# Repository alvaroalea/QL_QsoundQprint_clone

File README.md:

# SINCLAIR QL QsoundQprint Sound and Paralel Printer port interface

(C) 2022 Alvaro Alea Fernandez

License under: CERN Open Hardware Licence Version 2 - Strongly Reciprocal

https://ohwr.org/cern_ohl_s_v2.txt

I try to follow the original desing as much as possible, with some licenses:

- It's 10mm short, to fit in a 10x10cm, that is a lot cheaps if order PCB.
- The 7805 regulator board and the output Jack was modify.
- I use a electrolitic capacitor instead the original tantalo one.
- There are some jumper to allow a future ACB stereo mix.

This project can not be possible without the help of silvester, that tracked a fault in the schematic and Marcel Kilgus that develop a new ROM with a qsound device and a pt3 player.

I test with ROM versions 1.10, 1.31 and 1.40 and work as expected, new ROM do not have the printer routines, but have a new options used by the pt3 player. 

You can use a 2764 eprom or a W27C512 flash, that is much more cheap and easy to use.

This board user the default Motorola 68K inteface as described in the documentation of AY-3-8910 PSG. with a 6821 PIA as a glue between the QL and the PSG, in the info folder you can found aditional information about this chips or the interface.

The card have full 8bit I/O in the PSG without use, and another 8 bits in the PIA, also the pins of the paralel port are directly wired to the PSG, and are bidirectional, so can be used for other propouses.

The board use the E signal as a clock for the PSG, this cause that the PSG work in a very low frecuency, below the minimun indicated in the datasheet, and also this cause that tunes from Spectrum or other systems, can not be directly converted.

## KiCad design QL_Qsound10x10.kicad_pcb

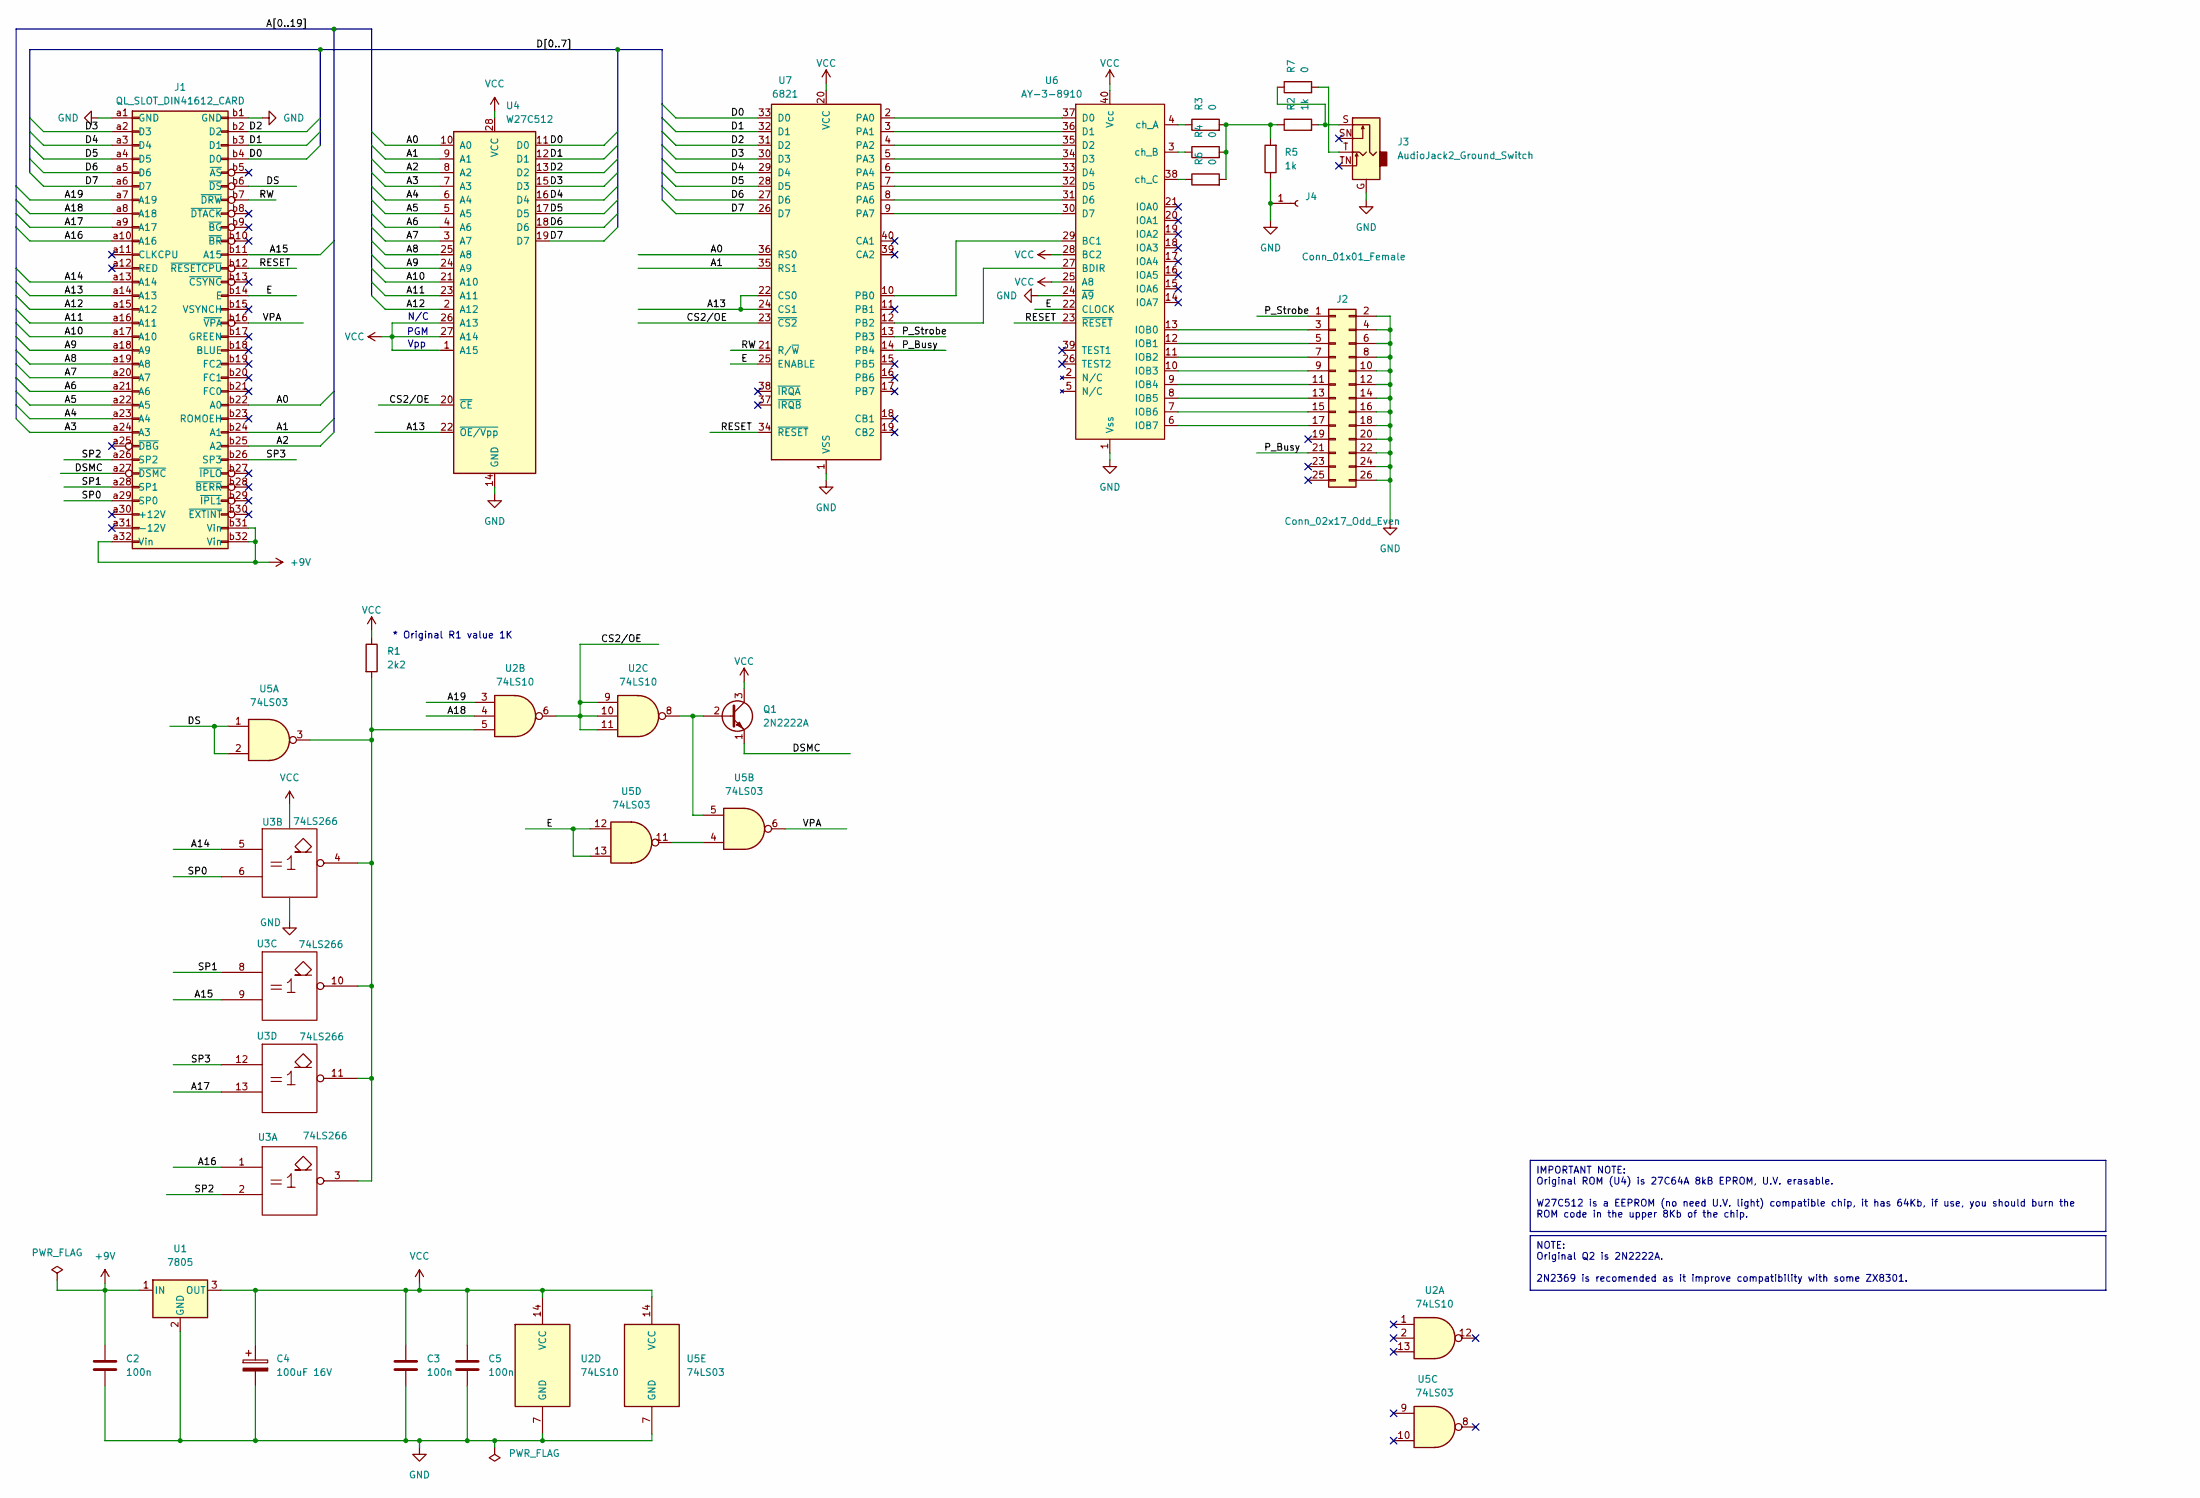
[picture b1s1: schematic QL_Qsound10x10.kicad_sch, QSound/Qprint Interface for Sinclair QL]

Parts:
C2, C3, C5: 100n; C_Disc_D4.3mm_W1.9mm_P5.00mm
C4: 100uF 16V; CP_Radial_D8.0mm_P5.00mm
J1: QL_SLOT_DIN41612_CARD; DIN41612_B_2x32_Female_Horizontal_THT
J2: Conn_02x17_Odd_Even; PinHeader_2x13_P2.54mm_Vertical
J3: AudioJack2_Ground_Switch
J4: Conn_01x01_Female; PinHeader_1x01_P2.54mm_Vertical
Q1: 2N2222A; TO-92_Inline
R1: 2k2; R_Axial_DIN0207_L6.3mm_D2.5mm_P7.62mm_Horizontal
R2, R5: 1k; R_Axial_DIN0207_L6.3mm_D2.5mm_P7.62mm_Horizontal
R3, R4, R6, R7: 0; R_Axial_DIN0207_L6.3mm_D2.5mm_P7.62mm_Horizontal
U1: 7805; TO-220-3_Horizontal_TabDown
U2: 74LS10; DIP-14_W7.62mm_LongPads
U3: 74LS266; DIP-14_W7.62mm_LongPads
U4: W27C512; DIP-28_W15.24mm_LongPads
U5: 74LS03; DIP-14_W7.62mm_LongPads
U6: AY-3-8910; DIP-40_W15.24mm_LongPads
U7: 6821; DIP-40_W15.24mm_LongPads

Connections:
+9V: C2.1, J1.a32 (Vin), J1.b31 (Vin), J1.b32 (Vin), U1.1 (IN)
/A0: J1.b22 (A0), U4.10 (A0), U7.36 (RS0)
/A1: J1.b24 (A1), U4.9 (A1), U7.35 (RS1)
/A2: J1.b25 (A2), U4.8 (A2)
/A3: J1.a24 (A3), U4.7 (A3)
/A4: J1.a23 (A4), U4.6 (A4)
/A5: J1.a22 (A5), U4.5 (A5)
/A6: J1.a21 (A6), U4.4 (A6)
/A7: J1.a20 (A7), U4.3 (A7)
/A8: J1.a19 (A8), U4.25 (A8)
/A9: J1.a18 (A9), U4.24 (A9)
/A10: J1.a17 (A10), U4.21 (A10)
/A11: J1.a16 (A11), U4.23 (A11)
/A12: J1.a15 (A12), U4.2 (A12)
/A13: J1.a14 (A13), U4.22 (~OE/Vpp), U7.22 (CS0), U7.24 (CS1)
/A14: J1.a13 (A14), U3.5
/A15: J1.b11 (A15), U3.9
/A16: J1.a10 (A16), U3.1
/A17: J1.a9 (A17), U3.13
/A18: J1.a8 (A18), U2.4
/A19: J1.a7 (A19), U2.3
/CS2/OE: U2.6, U2.9, U2.10, U2.11, U4.20 (~CE), U7.23 (~CS2)
/D0: J1.b4 (D0), U4.11 (D0), U7.33 (D0)
/D1: J1.b3 (D1), U4.12 (D1), U7.32 (D1)
/D2: J1.b2 (D2), U4.13 (D2), U7.31 (D2)
/D3: J1.a2 (D3), U4.15 (D3), U7.30 (D3)
/D4: J1.a3 (D4), U4.16 (D4), U7.29 (D4)
/D5: J1.a4 (D5), U4.17 (D5), U7.28 (D5)
/D6: J1.a5 (D6), U4.18 (D6), U7.27 (D6)
/D7: J1.a6 (D7), U4.19 (D7), U7.26 (D7)
/DS: J1.b6 (~DS), U5.1, U5.2
/DSMC: J1.a27 (~DSMC), Q1.1 (E)
/E: J1.b14 (E), U5.12, U5.13, U6.22 (CLOCK), U7.25 (ENABLE)
/P_Busy: J2.21, U7.14 (PB4)
/P_Strobe: J2.1, U7.13 (PB3)
/RESET: J1.b12 (~RESETCPU), U6.23 (~RESET), U7.34 (~RESET)
/RW: J1.b7 (~DRW), U7.21 (R/~W)
/SP0: J1.a29 (SP0), U3.6
/SP1: J1.a28 (SP1), U3.8
/SP2: J1.a26 (SP2), U3.2
/SP3: J1.b26 (SP3), U3.12
/VPA: J1.b16 (~VPA), U5.6
GND: C2.2, C3.2, C4.2, C5.2, J1.a1 (GND), J1.b1 (GND), J2.2, J2.4, J2.6, J2.8, J2.10, J2.12, J2.14, J2.16, J2.18, J2.20, J2.22, J2.24, J2.26, J3.G, J4.1, R5.1, U1.2 (GND), U2.7 (GND), U3.7 (GND), U4.14 (GND), U5.7 (GND), U6.1 (Vss), U6.24 (~A9), U7.1 (VSS)
unnamed: J2.3, U6.13 (IOB0)
unnamed: J2.5, U6.12 (IOB1)
unnamed: J2.7, U6.11 (IOB2)
unnamed: J2.9, U6.10 (IOB3)
unnamed: J2.11, U6.9 (IOB4)
unnamed: J2.13, U6.8 (IOB5)
unnamed: J2.15, U6.7 (IOB6)
unnamed: J2.17, U6.6 (IOB7)
unnamed: J3.S, R2.2, R7.1
unnamed: J3.T, R7.2
unnamed: Q1.2 (B), U2.8, U5.5
unnamed: R1.2, U2.5, U3.3, U3.4, U3.10, U3.11, U5.3
unnamed: R2.1, R3.2, R4.2, R5.2, R6.2
unnamed: U5.4, U5.11
unnamed: U6.29 (BC1), U7.10 (PB0)
unnamed: U6.27 (BDIR), U7.12 (PB2)
unnamed: U6.37 (D0), U7.2 (PA0)
unnamed: U6.36 (D1), U7.3 (PA1)
unnamed: U6.35 (D2), U7.4 (PA2)
unnamed: U6.34 (D3), U7.5 (PA3)
unnamed: U6.33 (D4), U7.6 (PA4)
unnamed: U6.32 (D5), U7.7 (PA5)
unnamed: U6.31 (D6), U7.8 (PA6)
unnamed: U6.30 (D7), U7.9 (PA7)
unnamed: R3.1, U6.4 (ch_A)
unnamed: R4.1, U6.3 (ch_B)
unnamed: R6.1, U6.38 (ch_C)
VCC: C3.1, C4.1, C5.1, Q1.3 (C), R1.1, U1.3 (OUT), U2.14 (VCC), U3.14 (VCC), U4.1 (A15), U4.26 (A13), U4.27 (A14), U4.28 (VCC), U5.14 (VCC), U6.25 (A8), U6.28 (BC2), U6.40 (Vcc), U7.20 (VCC)

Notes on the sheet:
NOTE: Original Q2 is 2N2222A. 2N2369 is recomended as it improve compatibility with some ZX8301.
IMPORTANT NOTE: Original ROM (U4) is 27C64A 8kB EPROM, U.V. erasable. W27C512 is a EEPROM (no need U.V. light) compatible chip, it has 64Kb, if use, you should burn the ROM code in the upper 8Kb of the chip.
Vpp
N/C
* Original R1 value 1K
PGM

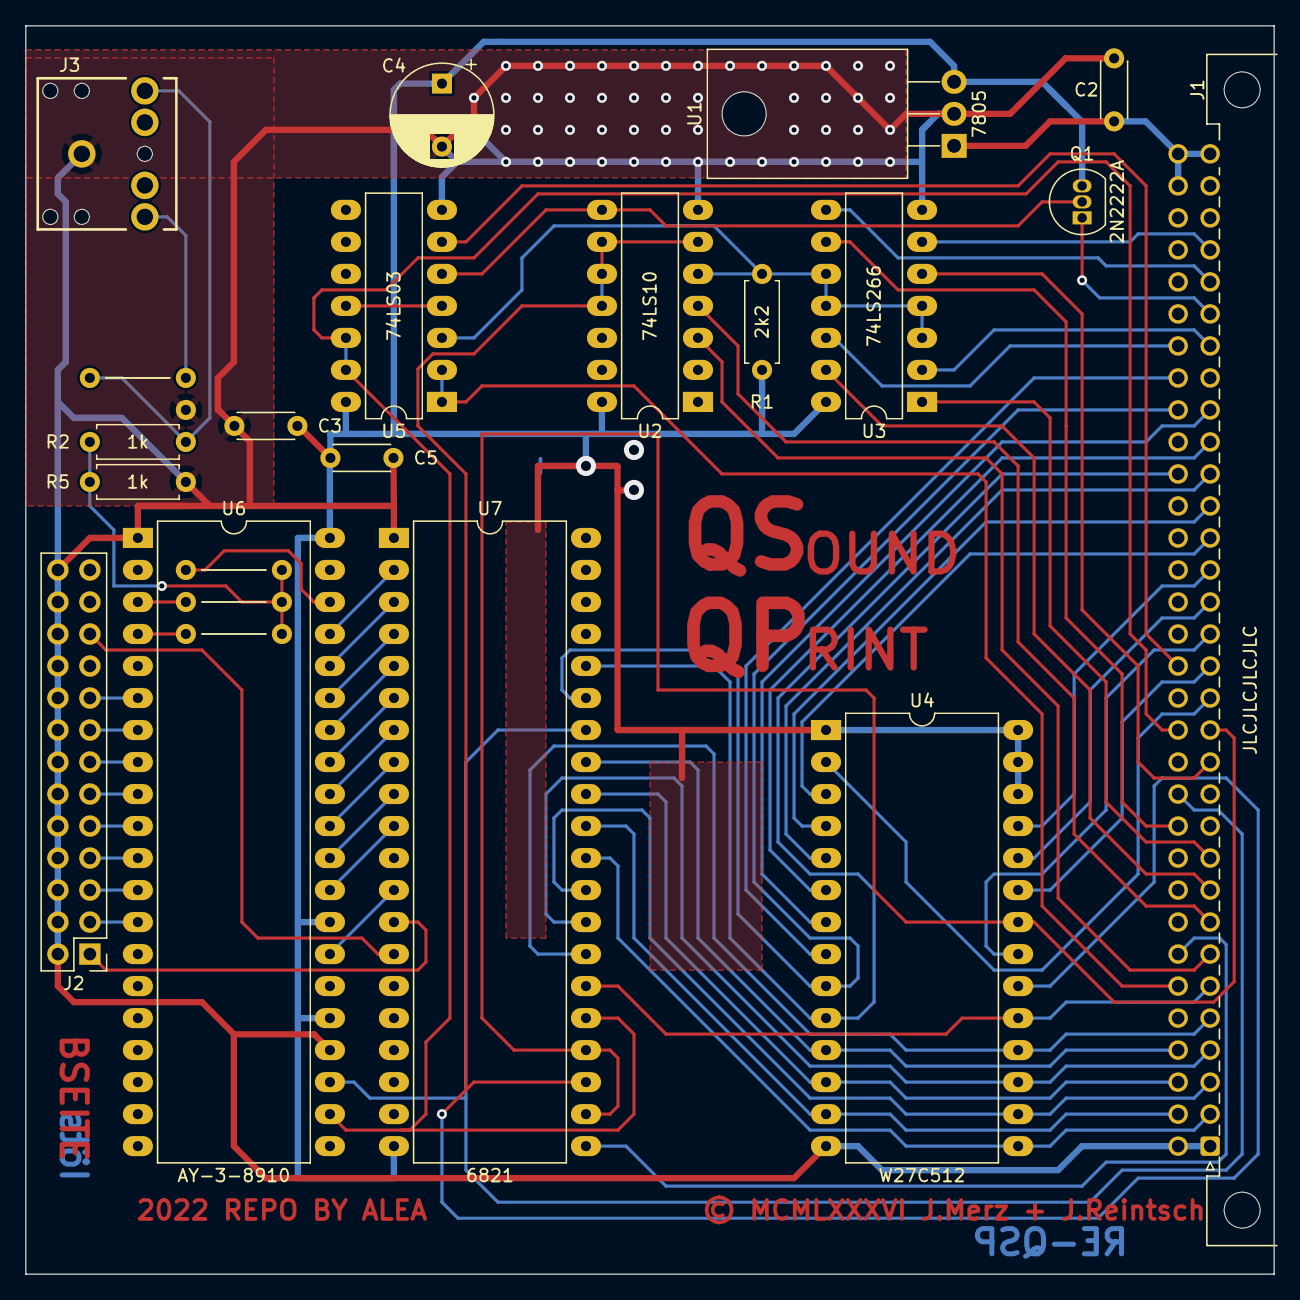
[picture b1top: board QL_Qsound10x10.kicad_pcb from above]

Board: 2 copper layers, 99.1 x 99.1 mm, 23 parts (0 on the bottom side), 71 nets.

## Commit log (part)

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2022-09-24 initial
2022-09-25 typo
2022-09-26 update info
2022-10-04 complete strings in pcb
2022-10-04 Noticia Importante, PCB mal
2022-10-11 Update, now work all
2022-10-12 tracks more similar to original
2023-11-19 Update some errors in PCB
2023-12-26 Updated pins on QL conector
2024-07-17 move 7805 down

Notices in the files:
QL_Qsound10x10.kicad_pcb:
© MCMLXXXVI J.Merz + J.Reintsch
